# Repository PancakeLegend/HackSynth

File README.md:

# HackSynth
A MODULAR SYNTH PROJECT

### PROJECT ORIGIN STORY
- WE DISCOVERED A VERY AWESOME BREADBOARD SYNTH PROJECT CALLED BS-1, BY SOMEONE CALLED MAXWELL BECK. 
- WE DECIDED TO CREATE A MODULAR SYNTH BASED ON THIS PROJECT, BUT DESIGN PCBS RATHER THAN USING BREADBOARDS FOR EACH MODULE

### WHAT IS THE PURPOSE OF THIS PROJECT?

### WHAT'S THE VISION?
- A LOW COST WAY FOR ENTHUSIASTS TO BREAK INTO THE WORLD OF MODULAR SYNTHESIS

### WHO ARE WE
- WE ARE MEMBERS AT THE CONNECTED COMMUNITY HACKERSPACE - A COMMUNITY FOR

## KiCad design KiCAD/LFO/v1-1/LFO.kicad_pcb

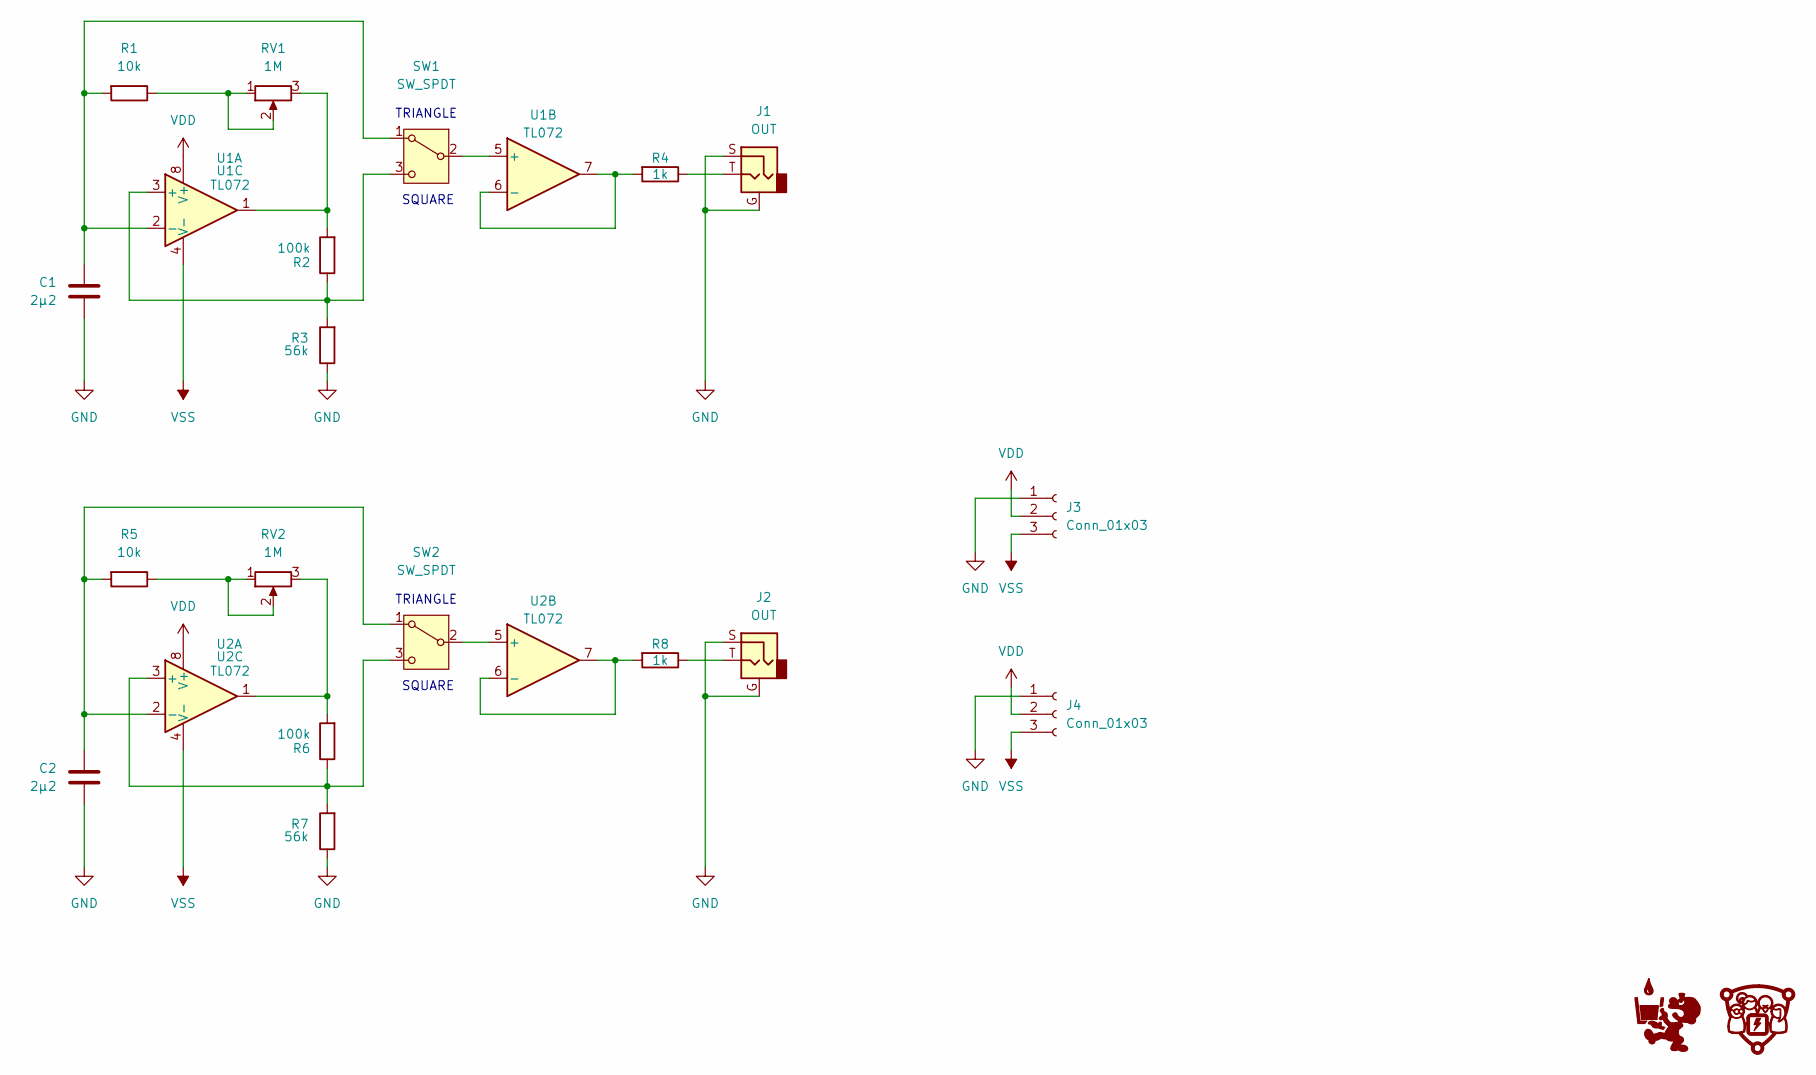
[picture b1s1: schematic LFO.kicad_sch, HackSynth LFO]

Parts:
C1, C2: 2µ2; C_Ceramic_D4.5mm_P5.00mm
G1, G2: (no value)
J1, J2: OUT; Jack_3.5mm
J3, J4: Conn_01x03; JST_PH_S3B-PH-K_1x03_P2.00mm_Horizontal
R1, R5: 10k; R_Axial_DIN0207_L6.3mm_D2.5mm_P7.62mm_Horizontal
R2, R6: 100k; R_Axial_DIN0207_L6.3mm_D2.5mm_P7.62mm_Horizontal
R3, R7: 56k; R_Axial_DIN0207_L6.3mm_D2.5mm_P7.62mm_Horizontal
R4, R8: 1k; R_Axial_DIN0207_L6.3mm_D2.5mm_P7.62mm_Horizontal
RV1, RV2: 1M; Potentiometer_Alps_RK09K_Horizontal
SW1, SW2: SW_SPDT; Switch SPDT - SMTS-102
U1, U2: TL072; DIP-8_W7.62mm_LongPads

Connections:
GND: C1.2, C2.2, J1.G, J1.S, J2.G, J2.S, J3.1, J4.1, R3.1, R7.1
unnamed: J1.T, R4.1
unnamed: J2.T, R8.1
unnamed: R1.1, RV1.1, RV1.2
unnamed: R2.2, RV1.3, U1.1
unnamed: R5.1, RV2.1, RV2.2
unnamed: R6.2, RV2.3, U2.1
unnamed: C1.1, R1.2, SW1.1 (A), U1.2 (-)
unnamed: SW1.2 (B), U1.5 (+)
unnamed: R2.1, R3.2, SW1.3 (C), U1.3 (+)
unnamed: C2.1, R5.2, SW2.1 (A), U2.2 (-)
unnamed: SW2.2 (B), U2.5 (+)
unnamed: R6.1, R7.2, SW2.3 (C), U2.3 (+)
unnamed: R4.2, U1.6 (-), U1.7
unnamed: R8.2, U2.6 (-), U2.7
VDD: J3.2, J4.2, U1.8 (V+), U2.8 (V+)
VSS: J3.3, J4.3, U1.4 (V-), U2.4 (V-)

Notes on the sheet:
SQUARE
TRIANGLE

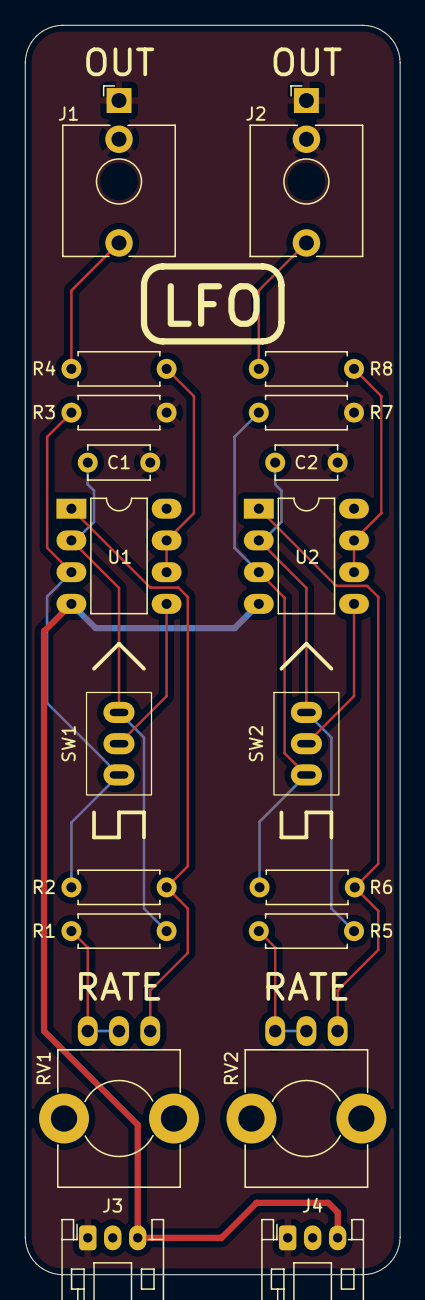
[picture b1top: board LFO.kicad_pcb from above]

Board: 2 copper layers, 30.0 x 100.0 mm, 21 parts (1 on the bottom side), 17 nets.

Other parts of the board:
Ref**: Val**; CCHS Logo - 10mm

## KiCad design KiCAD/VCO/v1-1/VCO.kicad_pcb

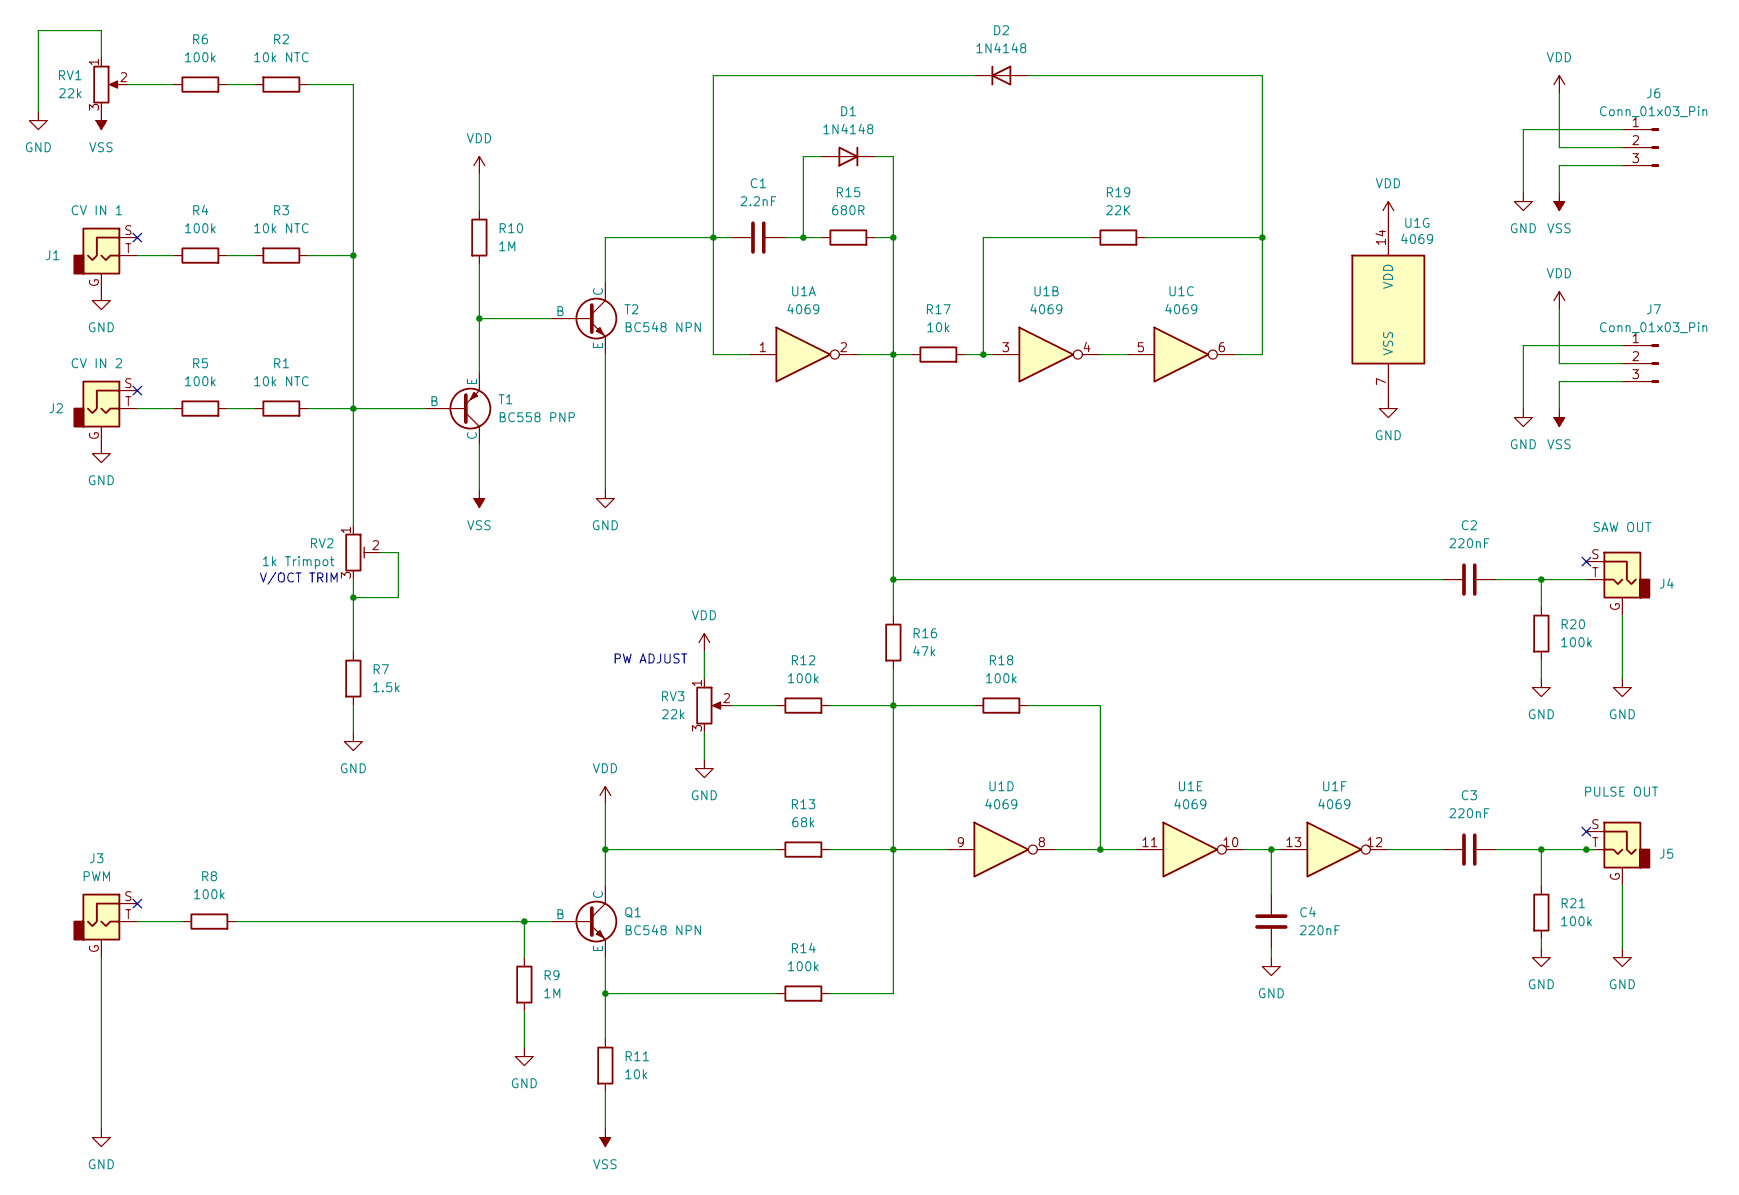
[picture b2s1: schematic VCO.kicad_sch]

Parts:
C1: 2.2nF; C_Disc_D5.0mm_W2.5mm_P2.50mm
C2, C3, C4: 220nF; C_Disc_D5.0mm_W2.5mm_P2.50mm
D1, D2: 1N4148; D_A-405_P7.62mm_Horizontal
J1: CV IN 1; Jack_3.5mm
J2: CV IN 2; Jack_3.5mm
J3: PWM; Jack_3.5mm
J4: SAW OUT; Jack_3.5mm
J5: PULSE OUT; Jack_3.5mm
J6, J7: Conn_01x03_Pin; JST_PH_S3B-PH-K_1x03_P2.00mm_Horizontal
Q1: BC548 NPN; TO-92_Inline - Handsolder
R1, R2, R3: 10k NTC; R_Axial_DIN0207_L6.3mm_D2.5mm_P2.54mm_Vertical
R4, R5, R6, R8, R12, R14, R18, R20, R21: 100k; R_Axial_DIN0207_L6.3mm_D2.5mm_P7.62mm_Horizontal
R7: 1.5k; R_Axial_DIN0207_L6.3mm_D2.5mm_P7.62mm_Horizontal
R9, R10: 1M; R_Axial_DIN0207_L6.3mm_D2.5mm_P7.62mm_Horizontal
R11, R17: 10k; R_Axial_DIN0207_L6.3mm_D2.5mm_P7.62mm_Horizontal
R13: 68k; R_Axial_DIN0207_L6.3mm_D2.5mm_P7.62mm_Horizontal
R15: 680R; R_Axial_DIN0207_L6.3mm_D2.5mm_P7.62mm_Horizontal
R16: 47k; R_Axial_DIN0207_L6.3mm_D2.5mm_P7.62mm_Horizontal
R19: 22K; R_Axial_DIN0207_L6.3mm_D2.5mm_P7.62mm_Horizontal
RV1, RV3: 22k; Potentiometer_Alps_RK09K_Horizontal
RV2: 1k Trimpot; TrimPot_Bourns_3339S_Horizontal
T1: BC558 PNP; TO-92_Inline - Handsolder
T2: BC548 NPN; TO-92_Inline - Handsolder
U1: 4069; DIP-14_W7.62mm_LongPads

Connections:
GND: C4.1, J1.G, J2.G, J3.G, J4.G, J5.G, J6.1, J7.1, R7.2, R9.2, R20.2, R21.2, RV1.1, RV3.3, T2.3 (E), U1.7 (VSS)
unnamed: C2.2, J4.T, R20.1
unnamed: C3.1, U1.12
unnamed: C3.2, J5.T, R21.1
unnamed: C4.2, U1.10, U1.13
unnamed: C1.2, D1.2 (A), R15.1
unnamed: C2.1, D1.1 (K), R15.2, R16.1, R17.1, U1.2
unnamed: D2.2 (A), R19.2, U1.6
unnamed: C1.1, D2.1 (K), T2.1 (C), U1.1
unnamed: J1.T, R4.1
unnamed: J2.T, R5.1
unnamed: J3.T, R8.1
unnamed: Q1.2 (B), R8.2, R9.1
unnamed: Q1.3 (E), R11.1, R14.1
unnamed: R1.1, R5.2
unnamed: R2.2, R6.2
unnamed: R3.2, R4.2
unnamed: R6.1, RV1.2
unnamed: R7.1, RV2.2, RV2.3
unnamed: R12.1, RV3.2
unnamed: R12.2, R13.2, R14.2, R16.2, R18.1, U1.9
unnamed: R17.2, R19.1, U1.3
unnamed: R18.2, U1.8, U1.11
unnamed: R1.2, R2.1, R3.1, RV2.1, T1.2 (B)
unnamed: R10.2, T1.3 (E), T2.2 (B)
unnamed: U1.4, U1.5
VDD: J6.2, J7.2, Q1.1 (C), R10.1, R13.1, RV3.1, U1.14 (VDD)
VSS: J6.3, J7.3, R11.2, RV1.3, T1.1 (C)

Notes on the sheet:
PW ADJUST
V/OCT TRIM

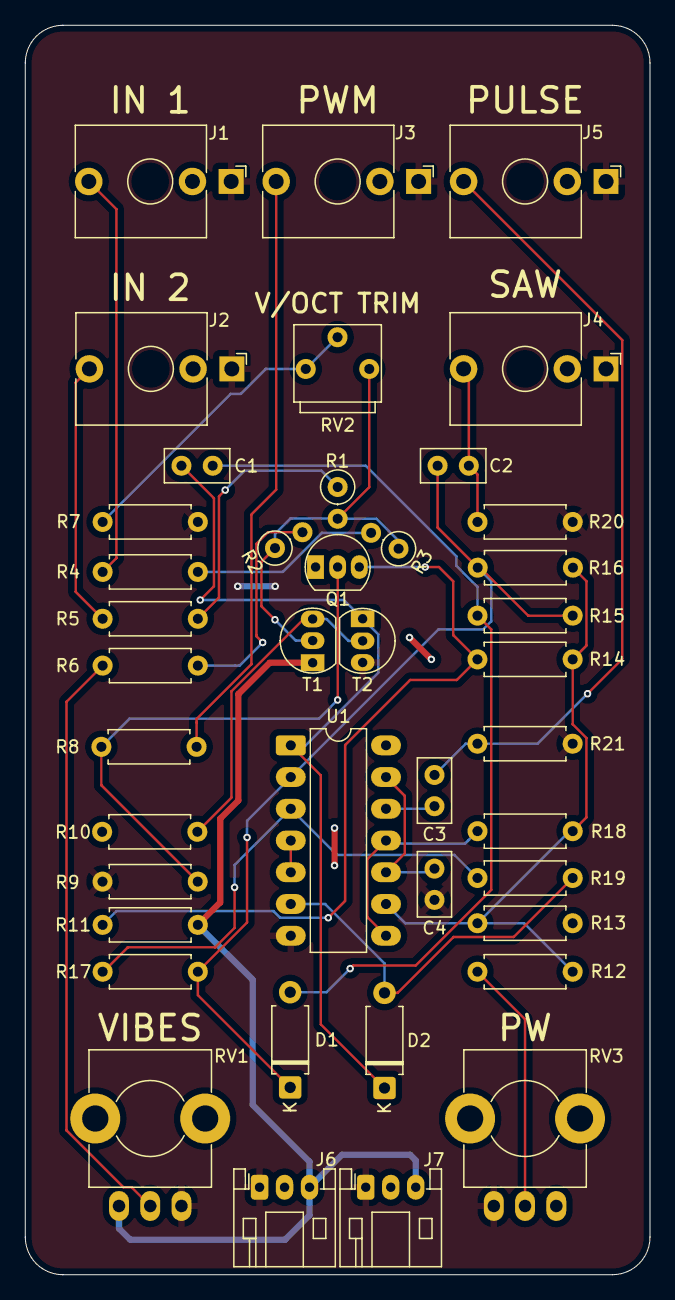
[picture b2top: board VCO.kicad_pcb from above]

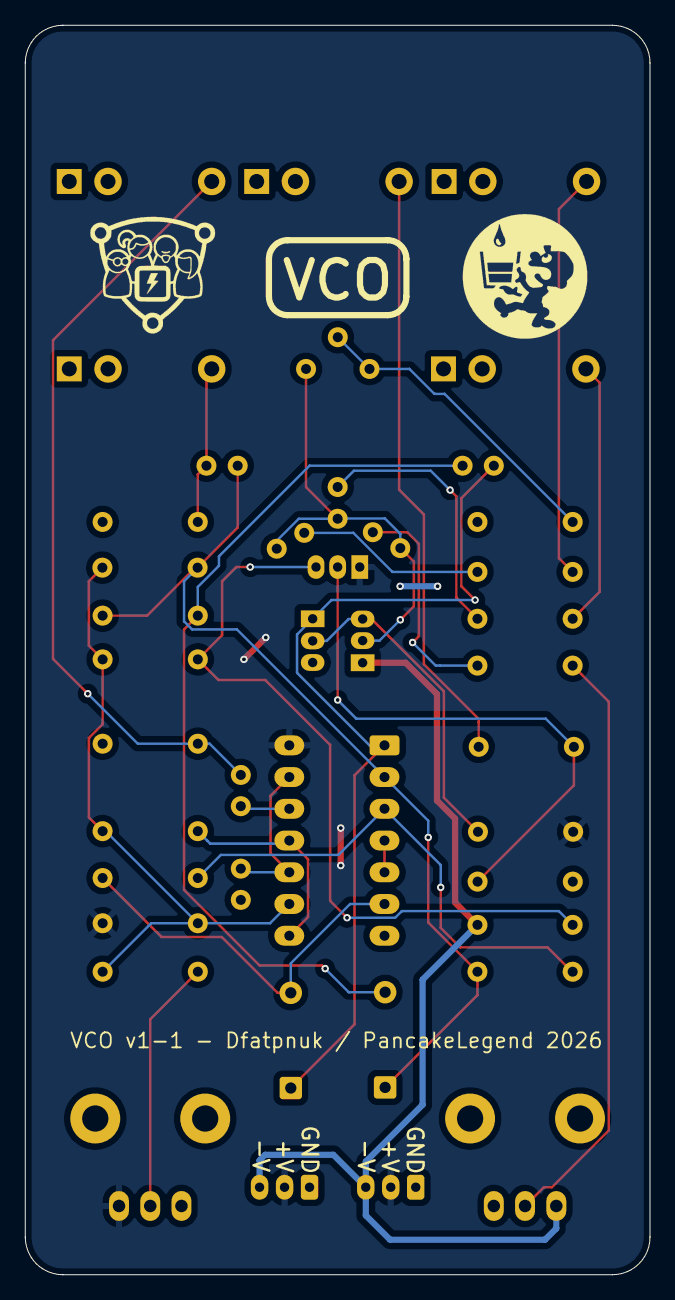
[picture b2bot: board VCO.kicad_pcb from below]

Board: 2 copper layers, 50.0 x 100.0 mm, 43 parts (2 on the bottom side), 28 nets.

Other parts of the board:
Ref**: Val**; CCHS Logo - 10mm
Ref**#2: Val**; PancakeLegend Logo - 10mm

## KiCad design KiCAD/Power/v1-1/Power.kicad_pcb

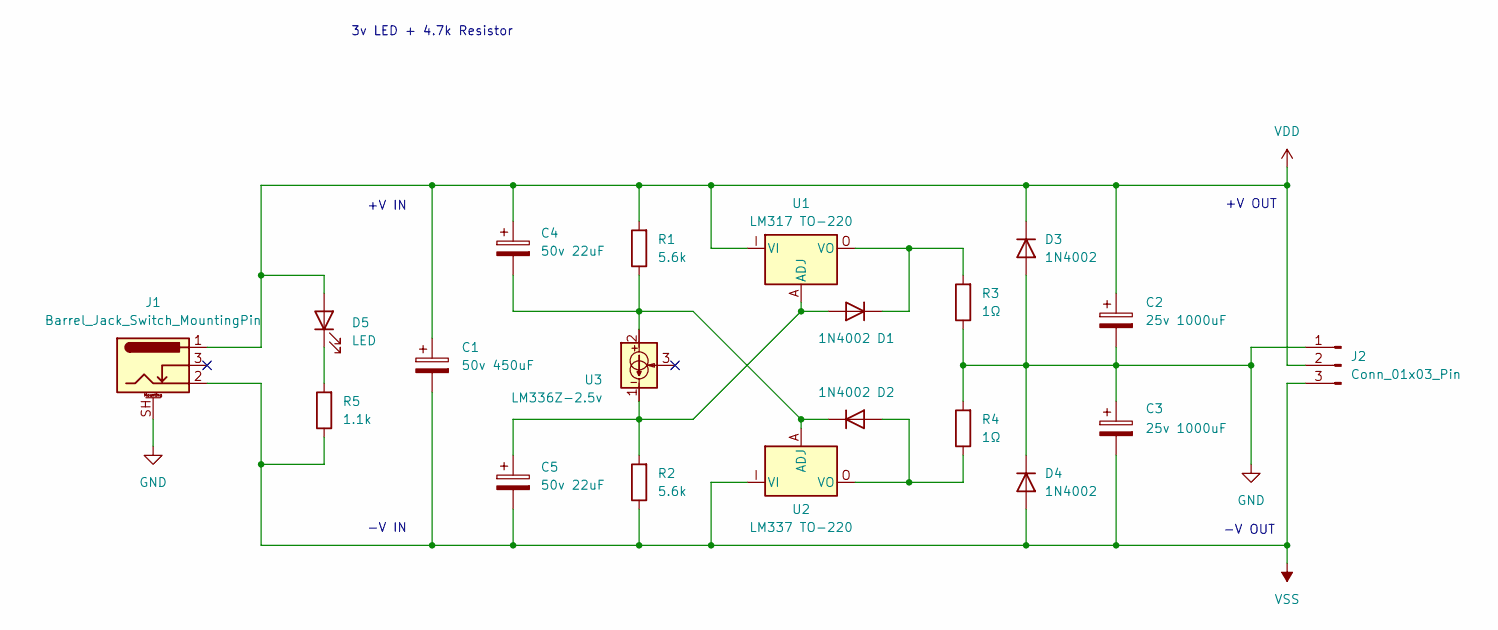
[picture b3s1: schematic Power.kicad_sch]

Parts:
C1: 50v 450uF; CP_Radial_D10.0mm_P5.00mm_MidMount
C2, C3: 25v 1000uF; CP_Radial_D10.0mm_P5.00mm_MidMount
C4, C5: 50v 22uF; CP_Radial_D5.2mm_P2.50mm_LayDown
D1, D2, D3, D4: 1N4002; D_A-405_P7.62mm_Horizontal
D5: LED; LED_D5.0mm
J1: Barrel_Jack_Switch_MountingPin; BarrelJack_DC044A
J2: Conn_01x03_Pin; JST_PH_S3B-PH-K_1x03_P2.00mm_Horizontal
R1, R2: 5.6k; R_Axial_DIN0207_L6.3mm_D2.5mm_P7.62mm_Horizontal
R3, R4: 1Ω; R_Axial_DIN0207_L6.3mm_D2.5mm_P7.62mm_Horizontal
R5: 1.1k; R_Axial_DIN0207_L6.3mm_D2.5mm_P7.62mm_Horizontal
U1: LM317 TO-220; LM317 - TO-220-3_Horizontal_TabDown
U2: LM337 TO-220; LM337 - TO-220-3_Horizontal_TabDown
U3: LM336Z-2.5v; TO-92_Inline - Handsolder

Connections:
GND: C2.2, C3.1, D3.2 (A), D4.1 (K), J1.SH (MountPin), J2.1, R3.1, R4.2
unnamed: C5.1, D1.2 (A), R2.2, U1.A (ADJ), U3.1
unnamed: D1.1 (K), R3.2, U1.O (VO)
unnamed: D2.2 (A), R4.1, U2.O (VO)
unnamed: C4.2, D2.1 (K), R1.1, U2.A (ADJ), U3.2
unnamed: D5.1 (K), R5.2
VDD: C1.1, C2.1, C4.1, D3.1 (K), D5.2 (A), J1.1, J2.2, R1.2, U1.I (VI)
VSS: C1.2, C3.2, C5.2, D4.2 (A), J1.2, J2.3, R2.1, R5.1, U2.I (VI)

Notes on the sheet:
3v LED + 4.7k Resistor
-V OUT
+V OUT
-V IN
+V IN

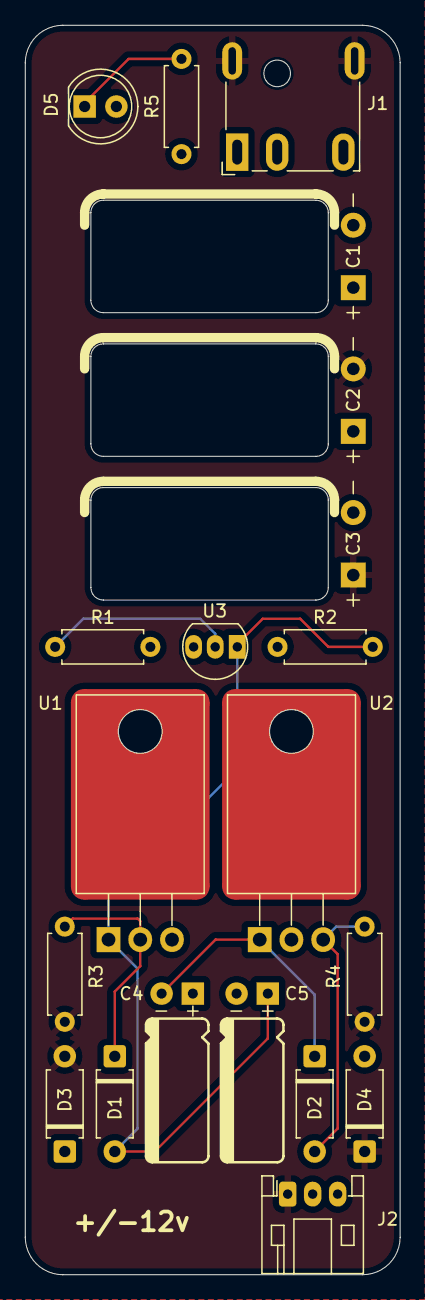
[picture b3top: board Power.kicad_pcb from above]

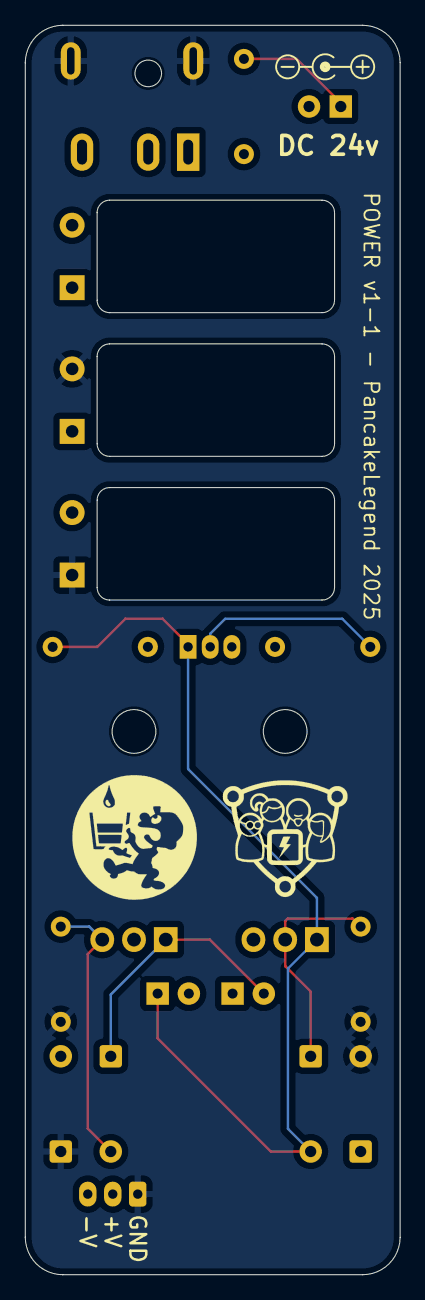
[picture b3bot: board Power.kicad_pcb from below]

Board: 4 copper layers, 30.0 x 100.0 mm, 22 parts (2 on the bottom side), 8 nets.

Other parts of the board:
Ref**: Val**; PancakeLegend Logo - 10mm
Ref**#2: Val**; CCHS Logo - 10mm

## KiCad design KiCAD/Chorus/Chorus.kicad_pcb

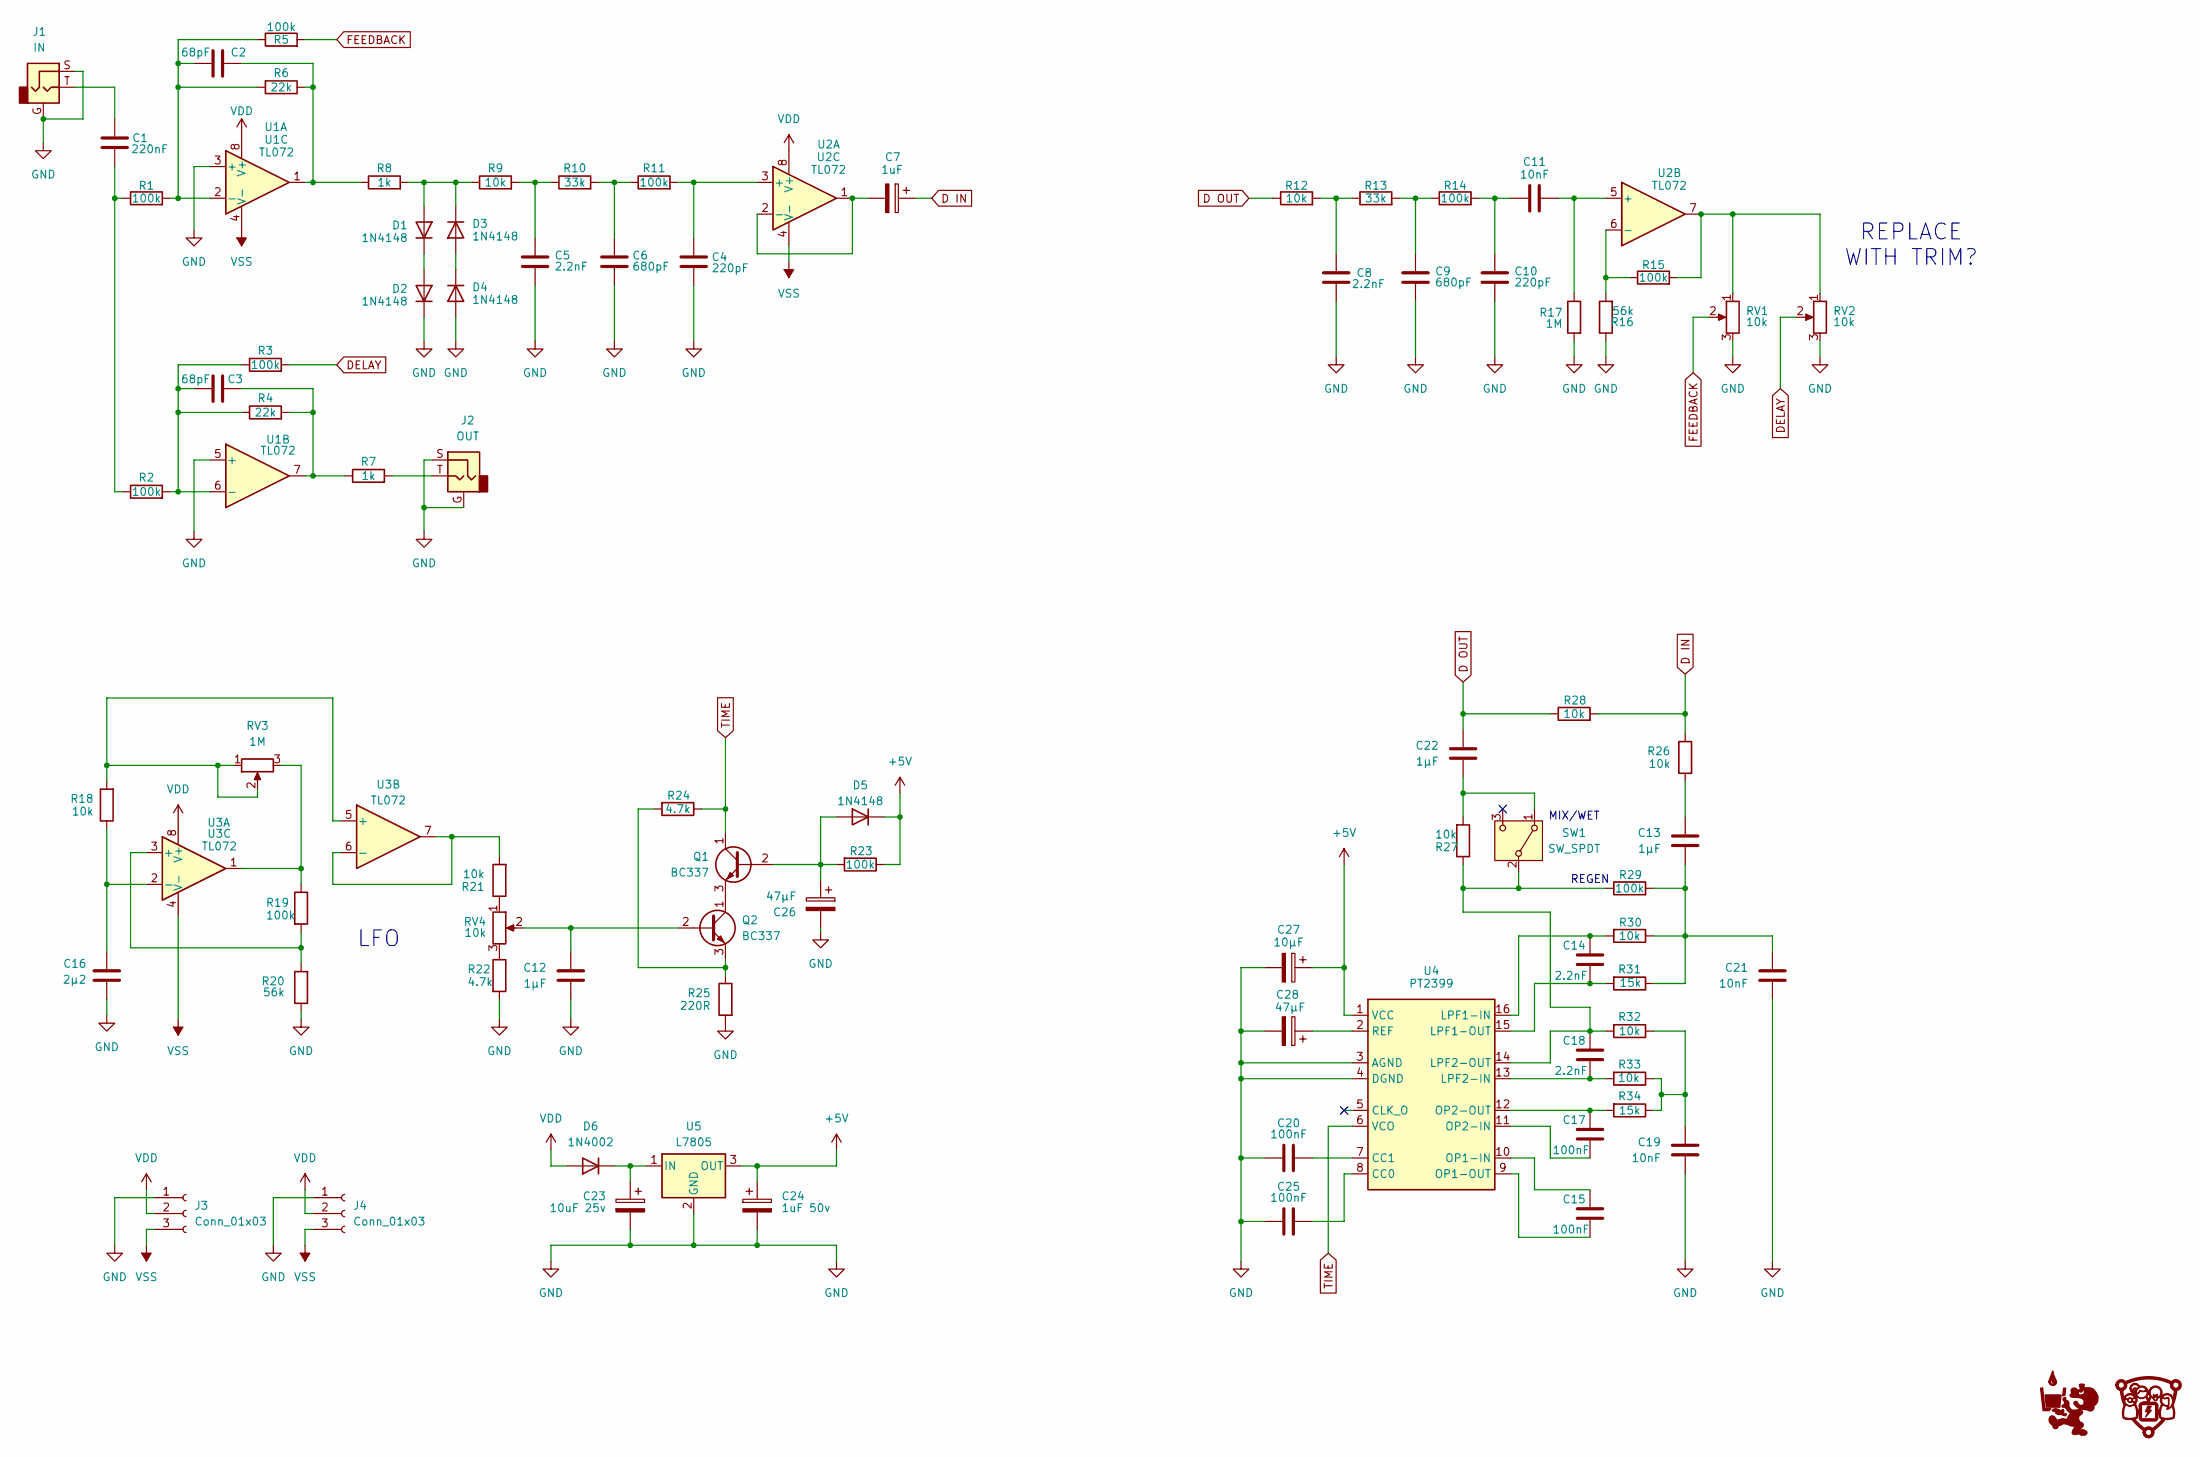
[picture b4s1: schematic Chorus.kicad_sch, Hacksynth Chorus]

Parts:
C1: 220nF; C_Ceramic_D4.5mm_P5.00mm
C2, C3: 68pF; C_Ceramic_D4.5mm_P5.00mm
C4, C10: 220pF; C_Ceramic_D4.5mm_P5.00mm
C5, C8, C14, C18: 2.2nF; C_Ceramic_D4.5mm_P5.00mm
C6, C9: 680pF; C_Ceramic_D4.5mm_P5.00mm
C7: 1uF; CP_Radial_D4.0mm_P1.50mm
C11, C19, C21: 10nF; C_Ceramic_D4.5mm_P5.00mm
C12, C13, C22: 1µF; C_Ceramic_D4.5mm_P5.00mm
C15, C17, C20, C25: 100nF; C_Ceramic_D4.5mm_P5.00mm
C16: 2µ2; C_Ceramic_D4.5mm_P5.00mm
C23: 10uF 25v; CP_Radial_D4.0mm_P1.50mm
C24: 1uF 50v; CP_Radial_D4.0mm_P1.50mm
C26, C28: 47µF; CP_Radial_D5.2mm_P2.50mm_LayDown
C27: 10µF; CP_Radial_D5.2mm_P2.50mm_LayDown_Mirror
D1, D2, D3, D4, D5: 1N4148; D_Vertical_P2.54mm
D6: 1N4002; D_A-405_P7.62mm_Horizontal
G1: Logo - CCHS 10mm
G2: Logo - PancakeLegend 10mm
J1: IN; Jack_3.5mm
J2: OUT; Jack_3.5mm
J3, J4: Conn_01x03; JST_PH_S3B-PH-K_1x03_P2.00mm_Horizontal
Q1, Q2: BC337; TO-92_Inline - Handsolder
R1, R2, R3, R5, R11, R14, R15, R19, R23, R29: 100k; R_Vertical_P2.54mm
R4, R6: 22k; R_Vertical_P2.54mm
R7, R8: 1k; R_Vertical_P2.54mm
R9, R12, R18, R21, R26, R27, R28, R30, R32, R33: 10k; R_Vertical_P2.54mm
R10, R13: 33k; R_Vertical_P2.54mm
R16, R20: 56k; R_Vertical_P2.54mm
R17: 1M; R_Vertical_P2.54mm
R22, R24: 4.7k; R_Vertical_P2.54mm
R25: 220R; R_Vertical_P2.54mm
R31, R34: 15k; R_Vertical_P2.54mm
RV1, RV2, RV4: 10k; Potentiometer_Alps_RK09K_Horizontal
RV3: 1M; Potentiometer_Alps_RK09K_Horizontal
SW1: SW_SPDT; Switch SPDT - SMTS-102
U1, U2, U3: TL072; DIP-8_W7.62mm_LongPads
U4: PT2399; DIP-16_W7.62mm_LongPads
U5: L7805; L7805 - TO-220-3_Horizontal_TabDown

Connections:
+5V: C24.1, C27.1, D5.1 (K), R23.1, U4.1 (VCC), U5.3 (OUT)
D IN: C7.1, R26.1, R28.2
D OUT: C22.1, R12.1, R28.1
DELAY: R3.2, RV2.2
FEEDBACK: R5.2, RV1.2
GND: C4.2, C5.2, C6.2, C8.1, C9.2, C10.2, C12.2, C16.2, C19.2, C20.2, C21.2, C23.2, C24.2, C25.2, C26.2, C27.2, C28.2, D2.1 (K), D4.2 (A), J1.G, J1.S, J2.G, J2.S, J3.1, J4.1, R16.1, R17.2, R20.1, R22.2, R25.2, RV1.3, RV2.3, U1.3 (+), U1.5 (+), U4.3 (AGND), U4.4 (DGND), U5.2 (GND)
unnamed: C1.1, R1.1, R2.1
unnamed: C1.2, J1.T
unnamed: C2.1, R6.1, R8.1, U1.1
unnamed: C3.2, R4.2, R7.1, U1.7
unnamed: C5.1, R9.2, R10.1
unnamed: C6.1, R10.2, R11.1
unnamed: C8.2, R12.2, R13.1
unnamed: C9.1, R13.2, R14.1
unnamed: C10.1, C11.1, R14.2
unnamed: C13.1, R26.2
unnamed: C13.2, C21.1, R29.2, R30.1, R31.1
unnamed: C19.1, R32.1, R33.1, R34.1
unnamed: D1.2 (A), D3.1 (K), R8.2, R9.1
unnamed: D1.1 (K), D2.2 (A)
unnamed: D3.2 (A), D4.1 (K)
unnamed: C26.1, D5.2 (A), Q1.2 (B), R23.2
unnamed: C23.1, D6.1 (K), U5.1 (IN)
unnamed: J2.T, R7.2
unnamed: Q1.3 (E), Q2.1 (C)
unnamed: C12.1, Q2.2 (B), RV4.2
unnamed: Q2.3 (E), R24.2, R25.1
unnamed: R15.2, RV1.1, RV2.1, U2.7
unnamed: R19.1, RV3.3, U3.1
unnamed: R21.1, RV4.1
unnamed: R22.1, RV4.3
unnamed: C22.2, R27.2, SW1.1 (A)
unnamed: C18.1, R27.1, R29.1, R32.2, SW1.2 (B), U4.14 (LPF2-OUT)
unnamed: C2.2, R1.2, R5.1, R6.2, U1.2 (-)
unnamed: C3.1, R2.2, R3.1, R4.1, U1.6 (-)
unnamed: C4.1, R11.2, U2.3 (+)
unnamed: C7.2, U2.1, U2.2 (-)
unnamed: C11.2, R17.1, U2.5 (+)
unnamed: R15.1, R16.2, U2.6 (-)
unnamed: R19.2, R20.2, U3.3 (+)
unnamed: C16.1, R18.1, U3.2 (-)
unnamed: R18.2, RV3.1, RV3.2, U3.5 (+)
unnamed: R21.2, U3.6 (-), U3.7
unnamed: C25.1, U4.8 (CC0)
unnamed: C20.1, U4.7 (CC1)
unnamed: C14.1, R30.2, U4.16 (LPF1-IN)
unnamed: C14.2, R31.2, U4.15 (LPF1-OUT)
unnamed: C18.2, R33.2, U4.13 (LPF2-IN)
unnamed: C15.1, U4.10 (OP1-IN)
unnamed: C15.2, U4.9 (OP1-OUT)
unnamed: C17.2, U4.11 (OP2-IN)
unnamed: C17.1, R34.2, U4.12 (OP2-OUT)
unnamed: C28.1, U4.2 (REF)
TIME: Q1.1 (C), R24.1, U4.6 (VCO)
VDD: D6.2 (A), J3.2, J4.2, U1.8 (V+), U2.8 (V+), U3.8 (V+)
VSS: J3.3, J4.3, U1.4 (V-), U2.4 (V-), U3.4 (V-)

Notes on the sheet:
MIX/WET
LFO
REPLACE WITH TRIM?
REGEN

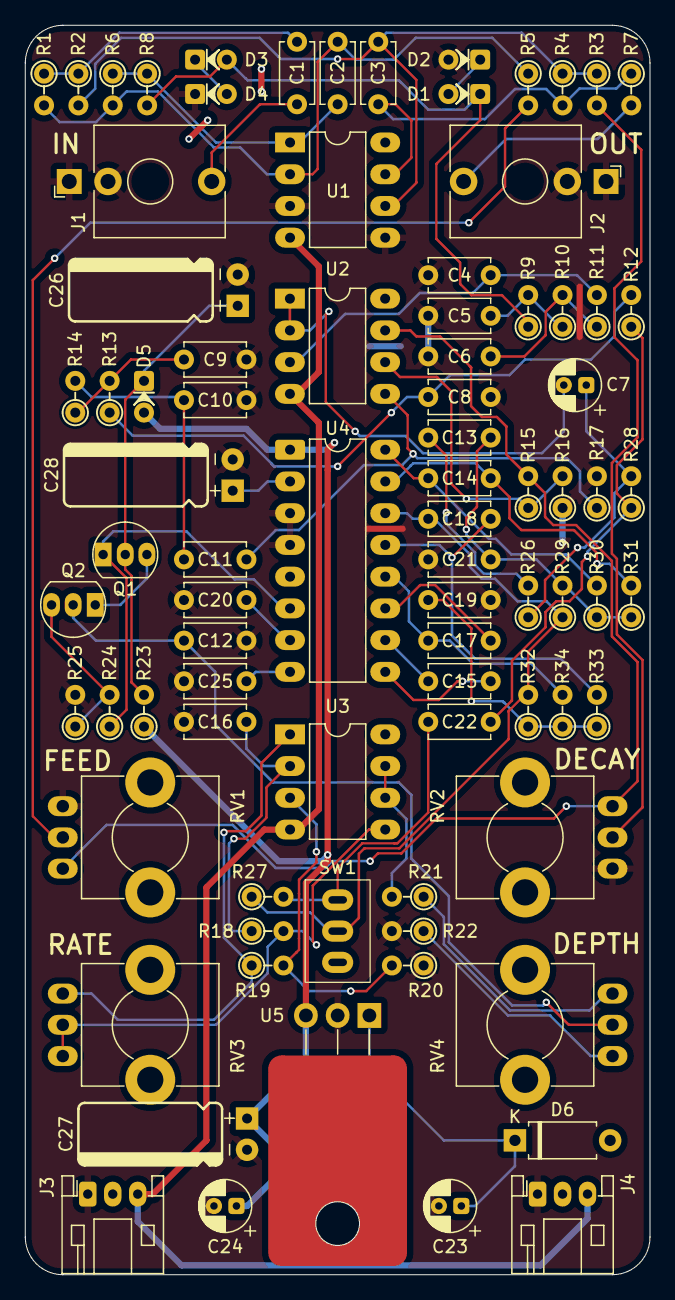
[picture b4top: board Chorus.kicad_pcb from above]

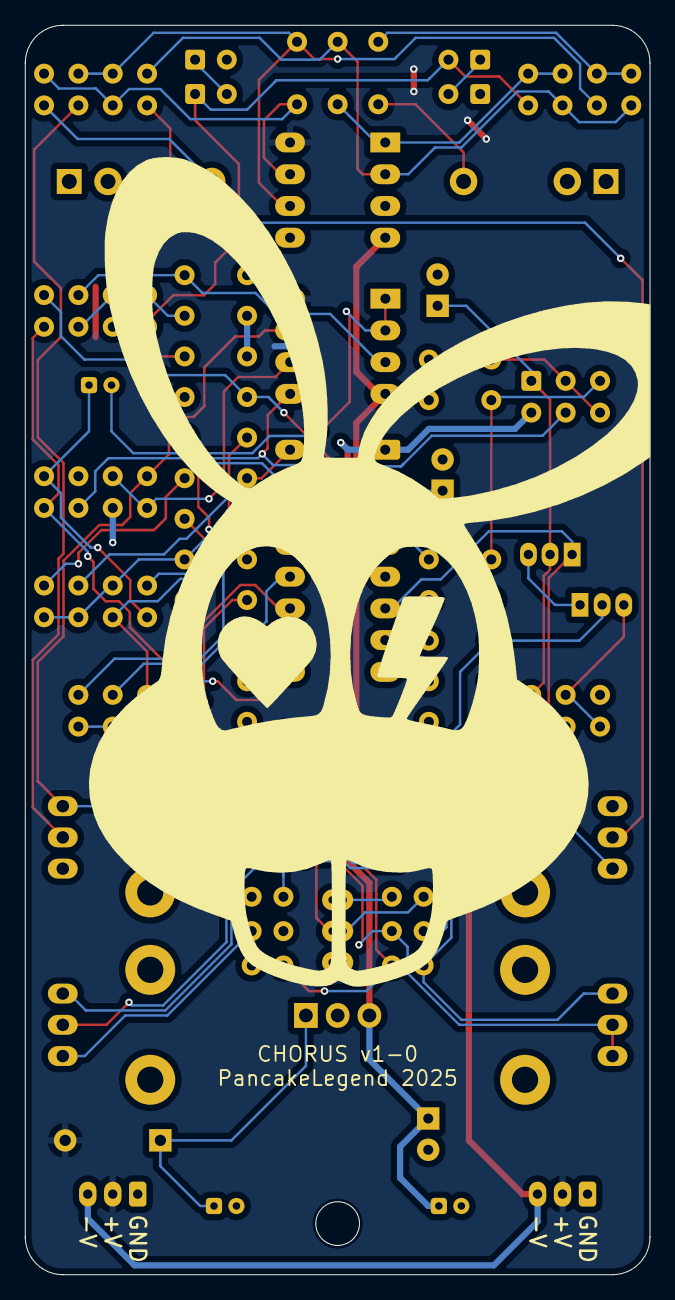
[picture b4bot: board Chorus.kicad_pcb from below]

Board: 2 copper layers, 50.0 x 100.0 mm, 86 parts (2 on the bottom side), 56 nets.
